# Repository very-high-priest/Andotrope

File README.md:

# Andotrope

Open Source andotrope I made, for anyone that wants to build their own andotrope.
Credit to the idea of an andotrope goes to Mike Ando https://www.riumplus.com/gehns-holographic-imager-andotrope/
I came up with the method of creating the see through effect.

This is just a prototype and certain things don't work properly yet, please read the issues.

We use a rp2040 zero as the main microcontroller.

Here's a link to the specific screens i bought: 
https://nl.aliexpress.com/item/1005004662221931.html?spm=a2g0o.order_list.order_list_main.45.342279d2Cq6V3n&gatewayAdapt=glo2nld

Here's the link for the specific battery I bought:
https://www.amazon.com.be/-/nl/Lithium-polymeer-batterij-oplaadbare-connector/dp/B09DPP44C4/ref=sr_1_49?crid=2DGCH3SFM7T9Y&dib=eyJ2IjoiMSJ9.8MRHN6nsjn6rWcUjpGMPrWY0j2xv0fPXTWYNxfWofMixROA2xrdyIJKaopa5pxHBBI75-L6SN22FPPGtZX5OZ7Z9TBroLJ-eeARtyQQAdxwKBCn1AIRiqlJuRBfy318Pp8mZ5ea26fVgcEUHzXKW4zh8m-2FN1g8nhIcIWSPJ6bxrBKwXuq9ip4Wns2wsEUuukwkeq4bNFK2VB0fXXlntxXlQ5qIdWuJtqNhckXLF4XL6SS-KhW8iBYEFRrPiUnk5ZcpyS0m8zIDaoi9WfFQu_M5-0GlCY70lMdHUPG0hWq-Ts-pe1UP6Gm08eo5E-oseqIPQL-jlwrKrjUD7YBSCnK23rQ5kJMaqqLZGjWuUO0.KSeEQlK2RLbnNdtz2xeDAL1vn8DUBxZG1J9pjteS1aU&dib_tag=se&keywords=lipo+batterij&qid=1739394303&refinements=p_n_feature_ten_browse-bin%3A28198239031&rnid=28197428031&s=electronics&sprefix=lipo+battterij%2Caps%2C61&sr=1-49&xpid=nX4bC5qjEs3Ko

Here's a link for the specific motor I bought:
https://nl.aliexpress.com/item/4001118243931.html?spm=a2g0o.order_list.order_list_main.50.342279d2Cq6V3n&gatewayAdapt=glo2nld 

Here's a link for the specific magnets I bought:
https://www.digikey.be/nl/products/detail/radial-magnets-inc/8996/5126078

Here's a link for the specific power connector I bought for the motor:
https://www.digikey.be/nl/products/detail/tensility-international-corp/54-00287/16649080 

The powerbrick isn't for sale anymore so you'll have to buy your own 6V barrel connector powerbrick.

Here's the link for the polarised film I used: 
https://nl.aliexpress.com/item/1005006054349865.html?spm=a2g0o.order_list.order_list_main.5.342279d2Cq6V3n&gatewayAdapt=glo2nld 

Unfortunately the screens themselves are polarised at a 45° angle so you'll have to add another polarisation filter on top if it polarising it horizontally or vertically so the wrap around filter doesn't block the light coming from the filter at the opposite side of the screen holder but only blocks light from the screen itself.

here's the heat inserts I used:
https://nl.aliexpress.com/item/1005003582355741.html?spm=a2g0o.order_list.order_list_main.23.342279d2Cq6V3n&gatewayAdapt=glo2nld

Here's the screws I used for the heat inserts:
https://nl.aliexpress.com/item/1005005070119421.html?spm=a2g0o.order_list.order_list_main.11.342279d2Cq6V3n&gatewayAdapt=glo2nld 

I sourced the powerswitch from old christmas lights and soldered it in between the batteries power line. 

The rest of the components you should be able to source from the bill of materials of the scematic.

Here's some more important tips:

Do not solder the mosfet to the bord but rather bridge the source and drain.
I myself glued the screens to the screen holder using double sided tape.
The polarised film has a protective film on both sides that needs to be removed, be carefull because one side of the film is very sticky and should be oriented inwards. This sticky side does help with sticking it to the screens but not to the outside of the screen holder. I used zip ties for that.

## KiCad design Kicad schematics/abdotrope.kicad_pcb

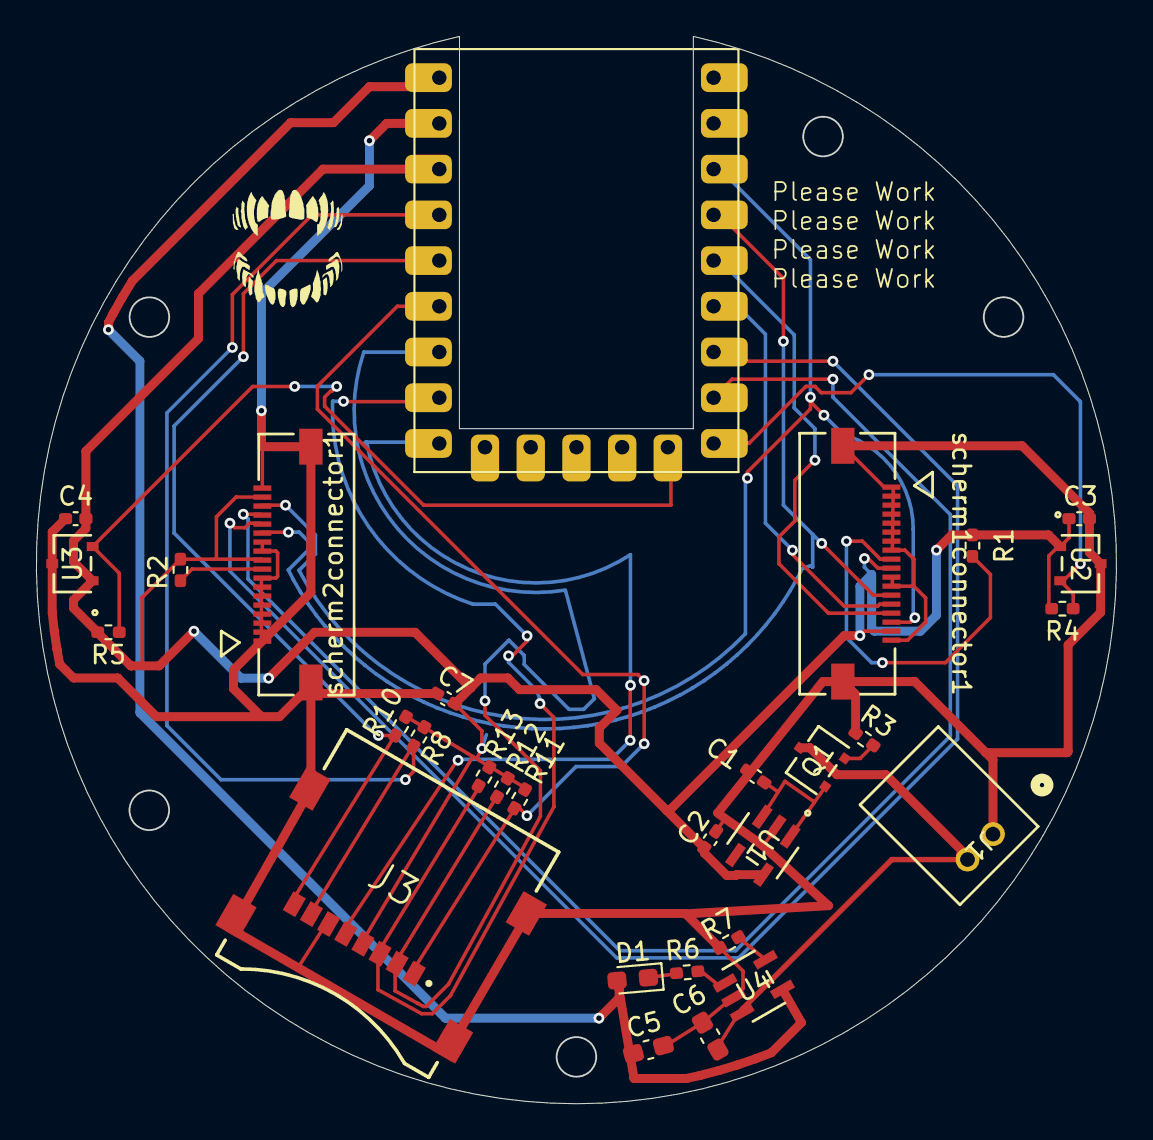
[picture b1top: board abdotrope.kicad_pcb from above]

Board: 2 copper layers, 60.0 x 59.3 mm, 30 parts (0 on the bottom side), 25 nets.

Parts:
C1, C2: 1 μF; C_0402_1005Metric_Pad0.74x0.62mm_HandSolder
C3, C4: 0.47 µF; C_0402_1005Metric_Pad0.74x0.62mm_HandSolder
C5, C6: 4,7 μF; C_0603_1608Metric_Pad1.08x0.95mm_HandSolder
C7: 100nF; C_0402_1005Metric_Pad0.74x0.62mm_HandSolder
D1: LED; LED_0603_1608Metric_Pad1.05x0.95mm_HandSolder
J1: S2B-PH-K-SLFSN; CONN_S2B-PH-K-S_JST
J3: MEM2067-02-180-00-A_REVB; GCT_MEM2067-02-180-00-A_REVB
Q1: PMOS (SSM3J372R); SOT-23F_TOS
R1, R2: 10; R_0402_1005Metric_Pad0.72x0.64mm_HandSolder
R3, R8, R10, R11, R12, R13: 10k; R_0402_1005Metric_Pad0.72x0.64mm_HandSolder
R4, R5: 4,7k; R_0402_1005Metric_Pad0.72x0.64mm_HandSolder
R6: 100; R_0402_1005Metric_Pad0.72x0.64mm_HandSolder
R7: 2.8k; R_0402_1005Metric_Pad0.72x0.64mm_HandSolder
RZ1: RP2040-Zero
U1: MIC5504-3.3YM5-TR; SOT-23-5_MC_MCH
U2, U3: TCS40DLR; SOT-23F_TOS
U4: MCP73831T-2ACI/OT; SOT-23-5_MC_MCH
scherm1connector1, scherm2connector1: 5051101892; CON_5051101892_MOL

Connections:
+3.3V: C2.1, C3.2, C4.2, C7.2, J3.4 (VDD), R1.2, R2.2, R4.2, R5.2, R8.1, R10.1, R11.1, R12.1, R13.1, RZ1.21 (3V3), U1.5 (VOUT), U2.1, U3.1, scherm1connector1.10, scherm1connector1.17, scherm2connector1.10, scherm2connector1.17
+5V: C5.1, D1.2 (A), RZ1.23 (GP28), U4.4 (VDD)
GND: C1.2, C2.2, C3.1, C4.1, C5.2, C6.2, C7.1, J1.1, J3.6 (VSS), J3.9 (SHIELD), J3.10 (SHIELD__1), J3.11 (SHIELD__2), J3.12 (SHIELD__3), R3.2, R7.1, RZ1.22 (GP29), U1.2 (GND), U2.3, U3.3, U4.2 (VSS), scherm1connector1.1, scherm1connector1.2, scherm1connector1.3, scherm1connector1.4, scherm1connector1.5, scherm1connector1.6, scherm1connector1.7, scherm1connector1.8, scherm1connector1.11, scherm1connector1.12, scherm1connector1.18, scherm1connector1.P1, scherm1connector1.P2, scherm2connector1.1, scherm2connector1.2, scherm2connector1.3, scherm2connector1.4, scherm2connector1.5, scherm2connector1.6, scherm2connector1.7, scherm2connector1.8, scherm2connector1.11, scherm2connector1.12, scherm2connector1.18, scherm2connector1.P1, scherm2connector1.P2
unnamed: D1.1 (K), R6.1
unnamed: J3.2 (CD/DAT3), R12.2, RZ1.17 (GP26)
unnamed: J3.5 (CLK), RZ1.15 (GP14)
unnamed: J3.3 (CMD), R13.2, RZ1.16 (GP15)
unnamed: J3.7 (DAT0), R8.2, RZ1.20 (GND)
unnamed: J3.8 (DAT1), R10.2, RZ1.19 (5V)
unnamed: J3.1 (DAT2), R11.2, RZ1.18 (GP27)
unnamed: C1.1, Q1.1 (D), U1.1 (VIN), U1.3 (EN)
unnamed: Q1.2 (G), R3.1
unnamed: C6.1, J1.2, Q1.3 (S), U4.3 (VBAT)
unnamed: R1.1, scherm1connector1.9
unnamed: R2.1, scherm2connector1.9
unnamed: RZ1.3 (GP2), scherm1connector1.16, scherm2connector1.16
unnamed: RZ1.4 (GP3), scherm1connector1.13, scherm2connector1.13
unnamed: RZ1.5 (GP4), scherm1connector1.15
unnamed: RZ1.6 (GP5), scherm1connector1.14
unnamed: RZ1.7 (GP6), scherm2connector1.14
unnamed: RZ1.8 (GP7), scherm2connector1.15
unnamed: R4.1, RZ1.9 (GP8), U2.2
unnamed: R5.1, RZ1.10 (GP9), U3.2
unnamed: R7.2, U4.5 (PROG)
unnamed: R6.2, U4.1 (STAT)

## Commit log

2025-07-27 Main files
    there is a spelling mistake in the kicad files I typed "abdotrope" instead of andotrope
2025-07-27 shopping list
    shopping list of things you'll need to buy and a couple tips when trying to build one
